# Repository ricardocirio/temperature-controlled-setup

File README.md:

# Temperature controlled setup

## About

This repository contains documentation for assembling a low-cost heating system designed for manufacturing and characterization of gas sensors, including dedicated hardware and firmware, comprising a proportional-integral-derivative controller and user interface for its use. The hardware consists of a printed circuit board containing an analog-to-digital converter (LTC2439) for temperature measurements acquired by thermocouples and a microcontroller (ATmega328P) that coordinates the entire process running a finite-state machine.

## Hardware

Full schematics may be found [here](./hardware/schematics.pdf). PCB's Kicad project is under the *hardware* folder.

## Authors

* Ricardo Cirio<br>
* Leticia Matos<br>
* Fernando Miranda<br>
* Daniel Lohmann

Sponsor: CNPq n° 04/2018.

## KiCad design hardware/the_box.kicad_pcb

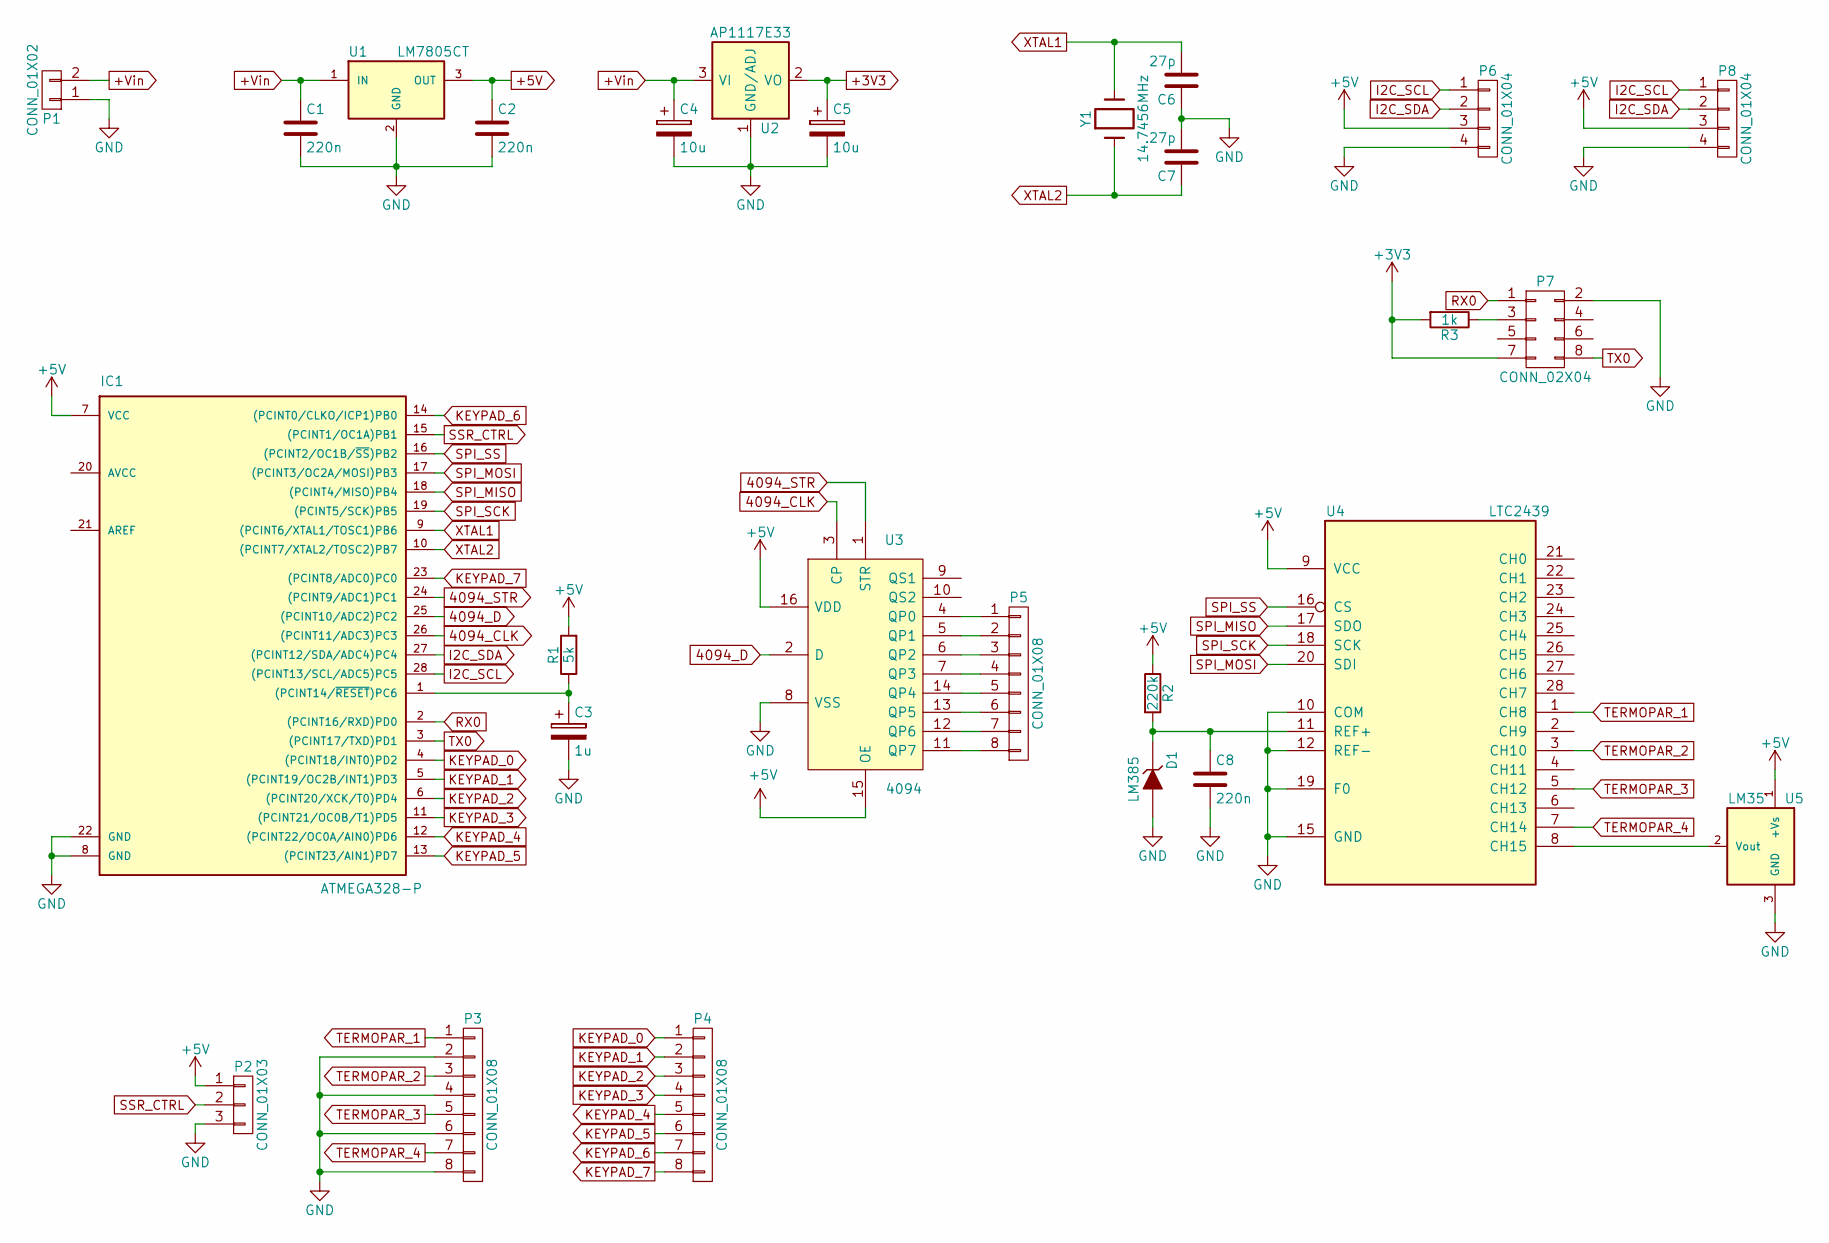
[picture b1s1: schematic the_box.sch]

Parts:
C1, C2, C8: 220n; C_0805_2012Metric_Pad1.15x1.40mm_HandSolder
C3: 1u; C_0805_2012Metric_Pad1.15x1.40mm_HandSolder
C4, C5: 10u; CP_Elec_6.3x5.3
C6, C7: 27p; C_0805_2012Metric_Pad1.15x1.40mm_HandSolder
D1: LM385; TO-92_Inline_Wide
IC1: ATMEGA328-P; DIP-28_W7.62mm_Socket_LongPads
P1: CONN_01X02; TerminalBlock_bornier-2_P5.08mm
P2: CONN_01X03; Molex_KK-254_AE-6410-03A_1x03_P2.54mm_Vertical
P3, P4: CONN_01X08; Molex_KK-254_AE-6410-08A_1x08_P2.54mm_Vertical
P5: CONN_01X08; PinHeader_1x08_P2.54mm_Vertical
P6, P8: CONN_01X04; Molex_KK-254_AE-6410-04A_1x04_P2.54mm_Vertical
P7: CONN_02X04; PinHeader_2x04_P2.54mm_Vertical
R1: 5k; R_1206_3216Metric_Pad1.42x1.75mm_HandSolder
R2: 220k; R_1206_3216Metric_Pad1.42x1.75mm_HandSolder
R3: 1k; R_0805_2012Metric_Pad1.15x1.40mm_HandSolder
U1: LM7805CT; TO-220-3_Vertical
U2: AP1117E33; SOT-223-3_TabPin2
U3: 4094; SOIC-16_3.9x9.9mm_P1.27mm
U4: LTC2439; SSOP-28_3.9x9.9mm_P0.635mm
U5: LM35; TO-92_Inline_Wide
Y1: 14.7456MHz; Crystal_HC49-U_Vertical

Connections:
4094_CLK: IC1.26 ((PCINT11/ADC3)PC3), U3.3 (CP)
4094_D: IC1.25 ((PCINT10/ADC2)PC2), U3.2 (D)
4094_STR: IC1.24 ((PCINT9/ADC1)PC1), U3.1 (STR)
+3V3: C5.1, P7.7, R3.2, U2.2 (VO)
+5V: C2.1, IC1.7 (VCC), P2.1, P6.3, P8.3, R1.2, R2.1, U1.3 (OUT), U3.15 (OE), U3.16 (VDD), U4.9 (VCC), U5.1 (+Vs)
+Vin: C1.1, C4.1, P1.2, U1.1 (IN), U2.3 (VI)
GND: C1.2, C2.2, C3.2, C4.2, C5.2, C6.1, C7.2, C8.2, D1.1 (A), IC1.8 (GND), IC1.22 (GND), P1.1, P2.3, P3.2, P3.4, P3.6, P3.8, P6.4, P7.2, P8.4, U1.2 (GND), U2.1 (GND/ADJ), U3.8 (VSS), U4.10 (COM), U4.12 (REF-), U4.15 (GND), U4.19 (F0), U5.3 (GND)
I2C_SCL: IC1.28 ((PCINT13/SCL/ADC5)PC5), P6.1, P8.1
I2C_SDA: IC1.27 ((PCINT12/SDA/ADC4)PC4), P6.2, P8.2
KEYPAD_0: IC1.4 ((PCINT18/INT0)PD2), P4.1
KEYPAD_1: IC1.5 ((PCINT19/OC2B/INT1)PD3), P4.2
KEYPAD_2: IC1.6 ((PCINT20/XCK/T0)PD4), P4.3
KEYPAD_3: IC1.11 ((PCINT21/OC0B/T1)PD5), P4.4
KEYPAD_4: IC1.12 ((PCINT22/OC0A/AIN0)PD6), P4.5
KEYPAD_5: IC1.13 ((PCINT23/AIN1)PD7), P4.6
KEYPAD_6: IC1.14 ((PCINT0/CLKO/ICP1)PB0), P4.7
KEYPAD_7: IC1.23 ((PCINT8/ADC0)PC0), P4.8
unnamed: C3.1, IC1.1 ((PCINT14/~RESET~)PC6), R1.1
unnamed: C8.1, D1.2 (K), R2.2, U4.11 (REF+)
unnamed: P5.1, U3.4 (QP0)
unnamed: P5.2, U3.5 (QP1)
unnamed: P5.3, U3.6 (QP2)
unnamed: P5.4, U3.7 (QP3)
unnamed: P5.5, U3.14 (QP4)
unnamed: P5.6, U3.13 (QP5)
unnamed: P5.7, U3.12 (QP6)
unnamed: P5.8, U3.11 (QP7)
unnamed: P7.3, R3.1
unnamed: U4.8 (CH15), U5.2 (Vout)
RX0: IC1.2 ((PCINT16/RXD)PD0), P7.1
SPI_MISO: IC1.18 ((PCINT4/MISO)PB4), U4.17 (SDO)
SPI_MOSI: IC1.17 ((PCINT3/OC2A/MOSI)PB3), U4.20 (SDI)
SPI_SCK: IC1.19 ((PCINT5/SCK)PB5), U4.18 (SCK)
SPI_SS: IC1.16 ((PCINT2/OC1B/~SS~)PB2), U4.16 (CS)
SSR_CTRL: IC1.15 ((PCINT1/OC1A)PB1), P2.2
TERMOPAR_1: P3.1, U4.1 (CH8)
TERMOPAR_2: P3.3, U4.3 (CH10)
TERMOPAR_3: P3.5, U4.5 (CH12)
TERMOPAR_4: P3.7, U4.7 (CH14)
TX0: IC1.3 ((PCINT17/TXD)PD1), P7.8
XTAL1: C6.2, IC1.9 ((PCINT6/XTAL1/TOSC1)PB6), Y1.2
XTAL2: C7.1, IC1.10 ((PCINT7/XTAL2/TOSC2)PB7), Y1.1

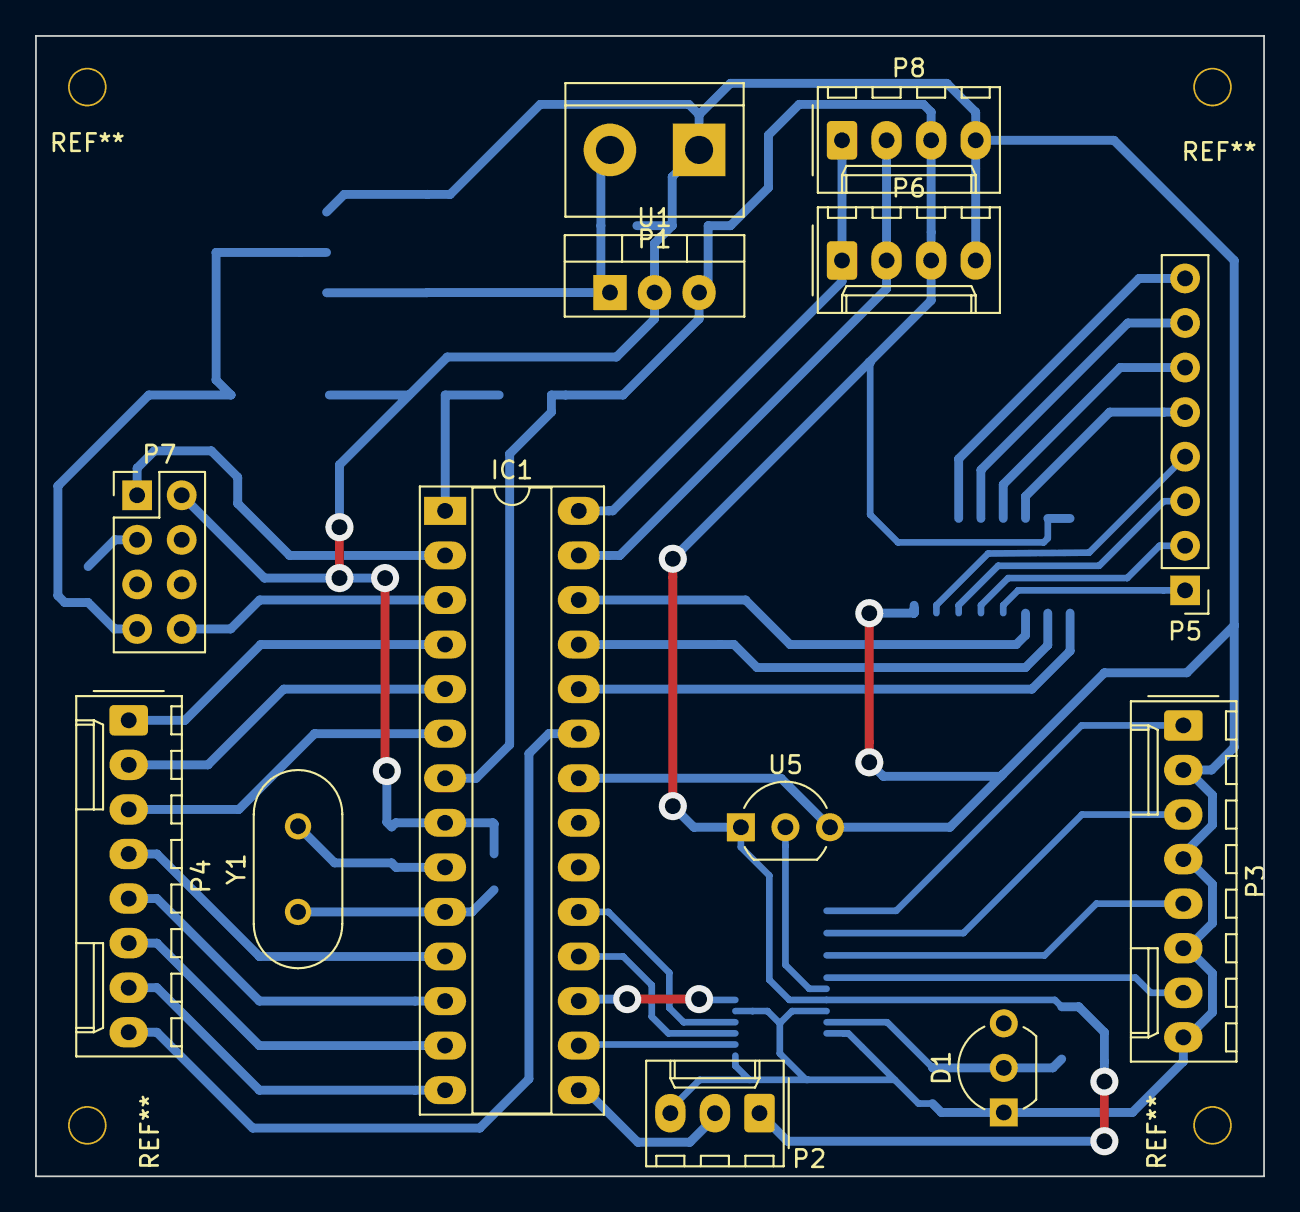
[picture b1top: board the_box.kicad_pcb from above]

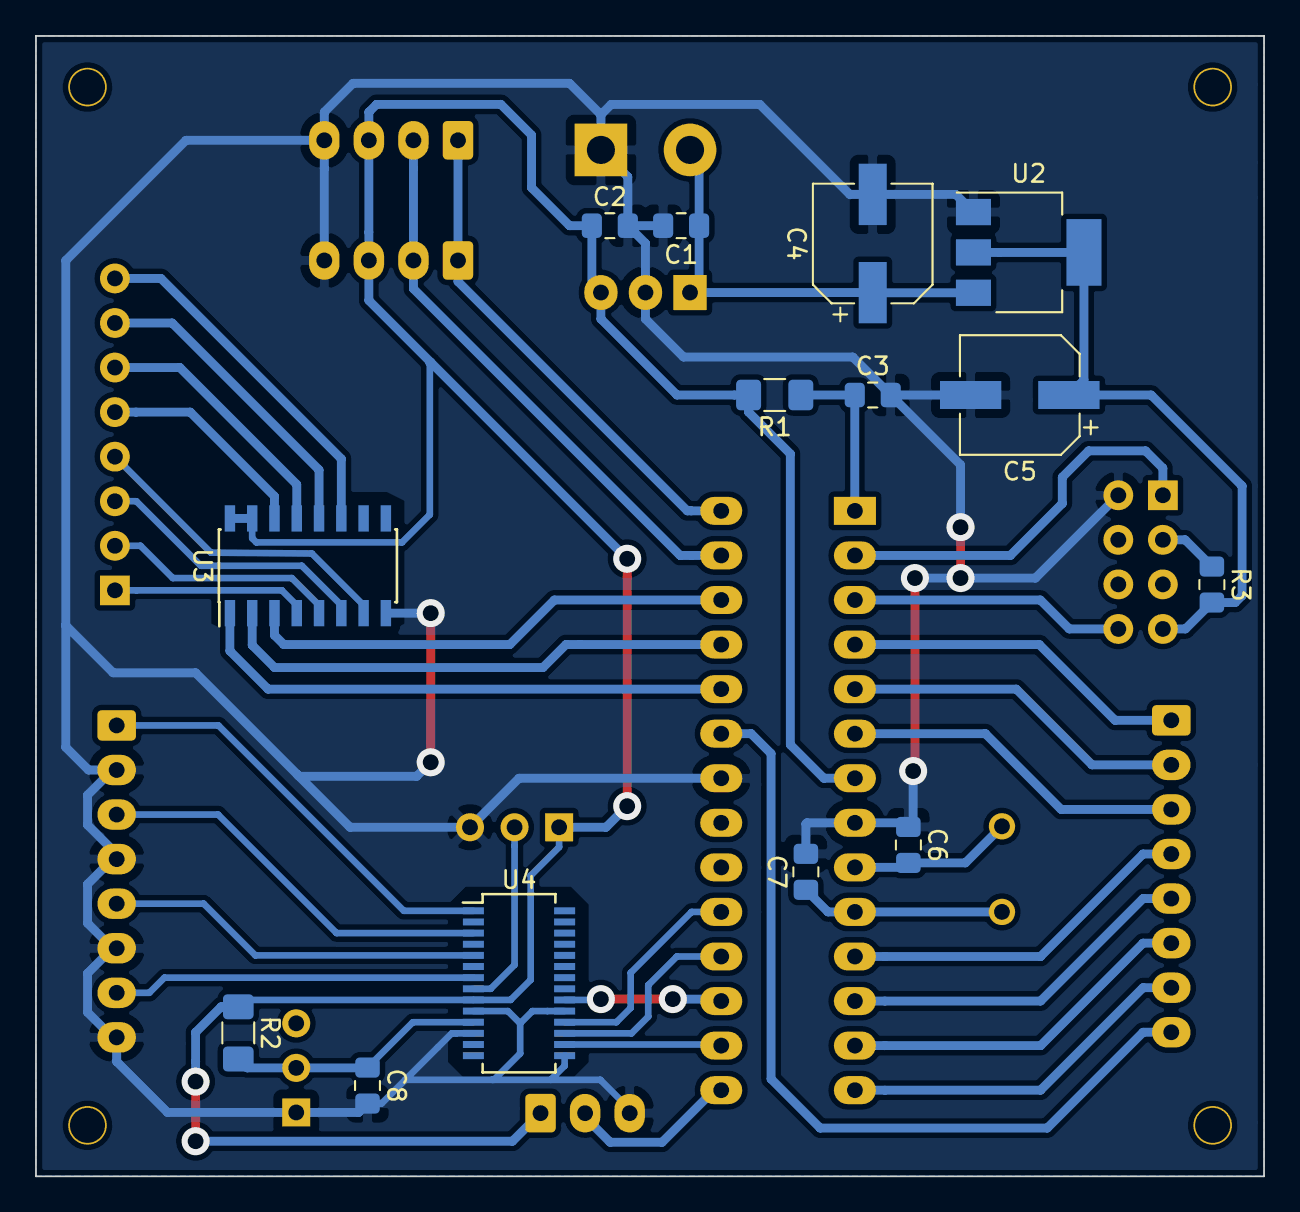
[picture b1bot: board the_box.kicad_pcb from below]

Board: 2 copper layers, 70.0 x 65.0 mm, 27 parts (14 on the bottom side), 42 nets.

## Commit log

2019-07-13 Initial commit.
2019-07-13 Added README
2019-07-13 Readme fix.
2019-07-13 Readme update.
